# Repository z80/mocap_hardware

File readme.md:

# TODO list for the verion 2.0

-[ ] Separate step down converters for a) MCU and I2C circuits and b) for bluetooth.
-[ ] I2C power filtering capacitors on every outgoung power line on RJ45 sockets.
-[ ] Correct MCU boot mode pins configuration so that it can be updated via USB.
-[ ] Larger filtering capacitors for the bluetooth module.
-[ ] 4 I2C sensors per one RJ45 socket.

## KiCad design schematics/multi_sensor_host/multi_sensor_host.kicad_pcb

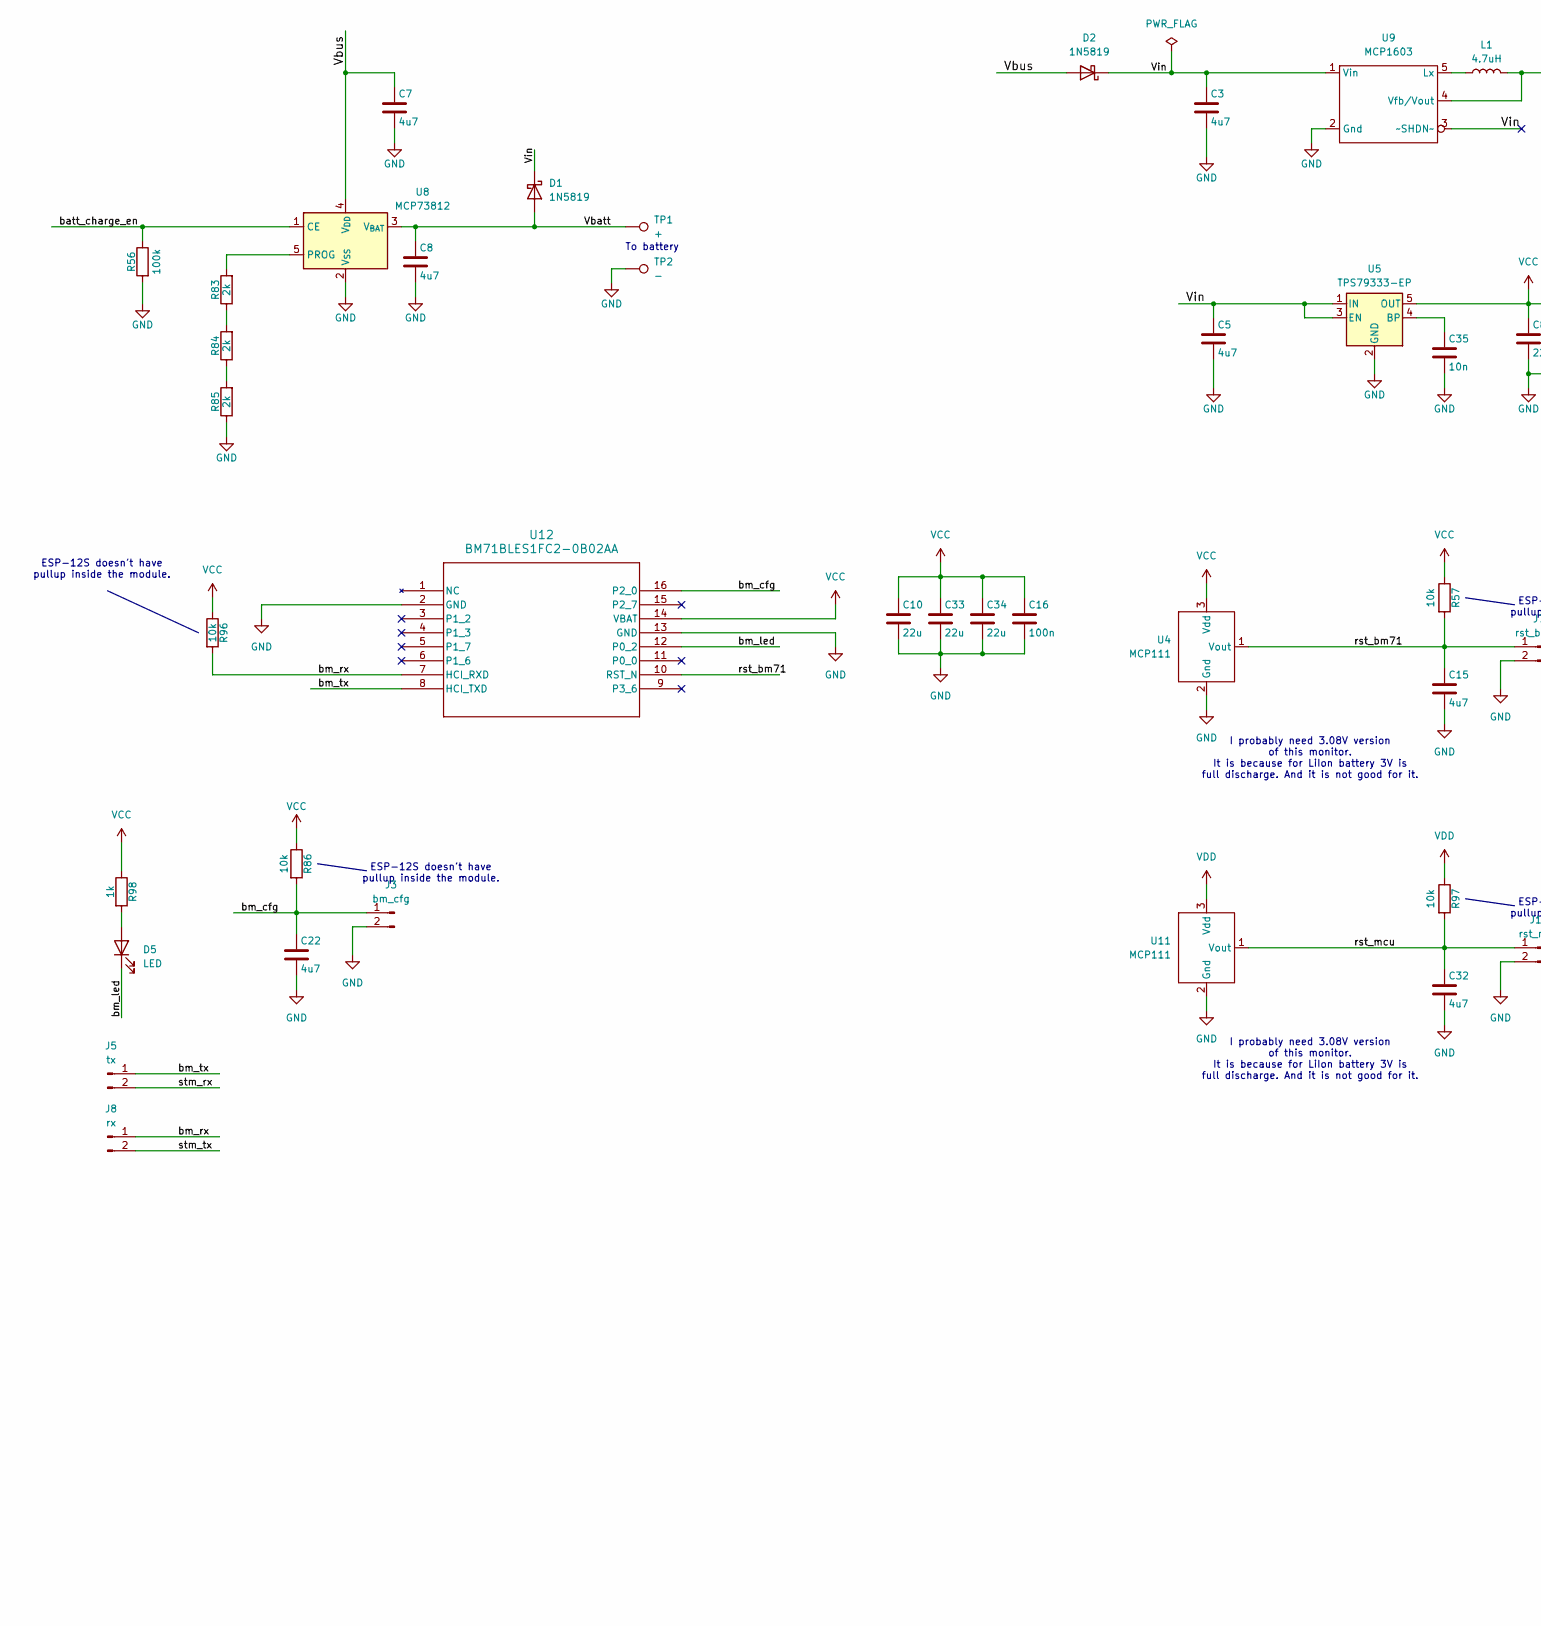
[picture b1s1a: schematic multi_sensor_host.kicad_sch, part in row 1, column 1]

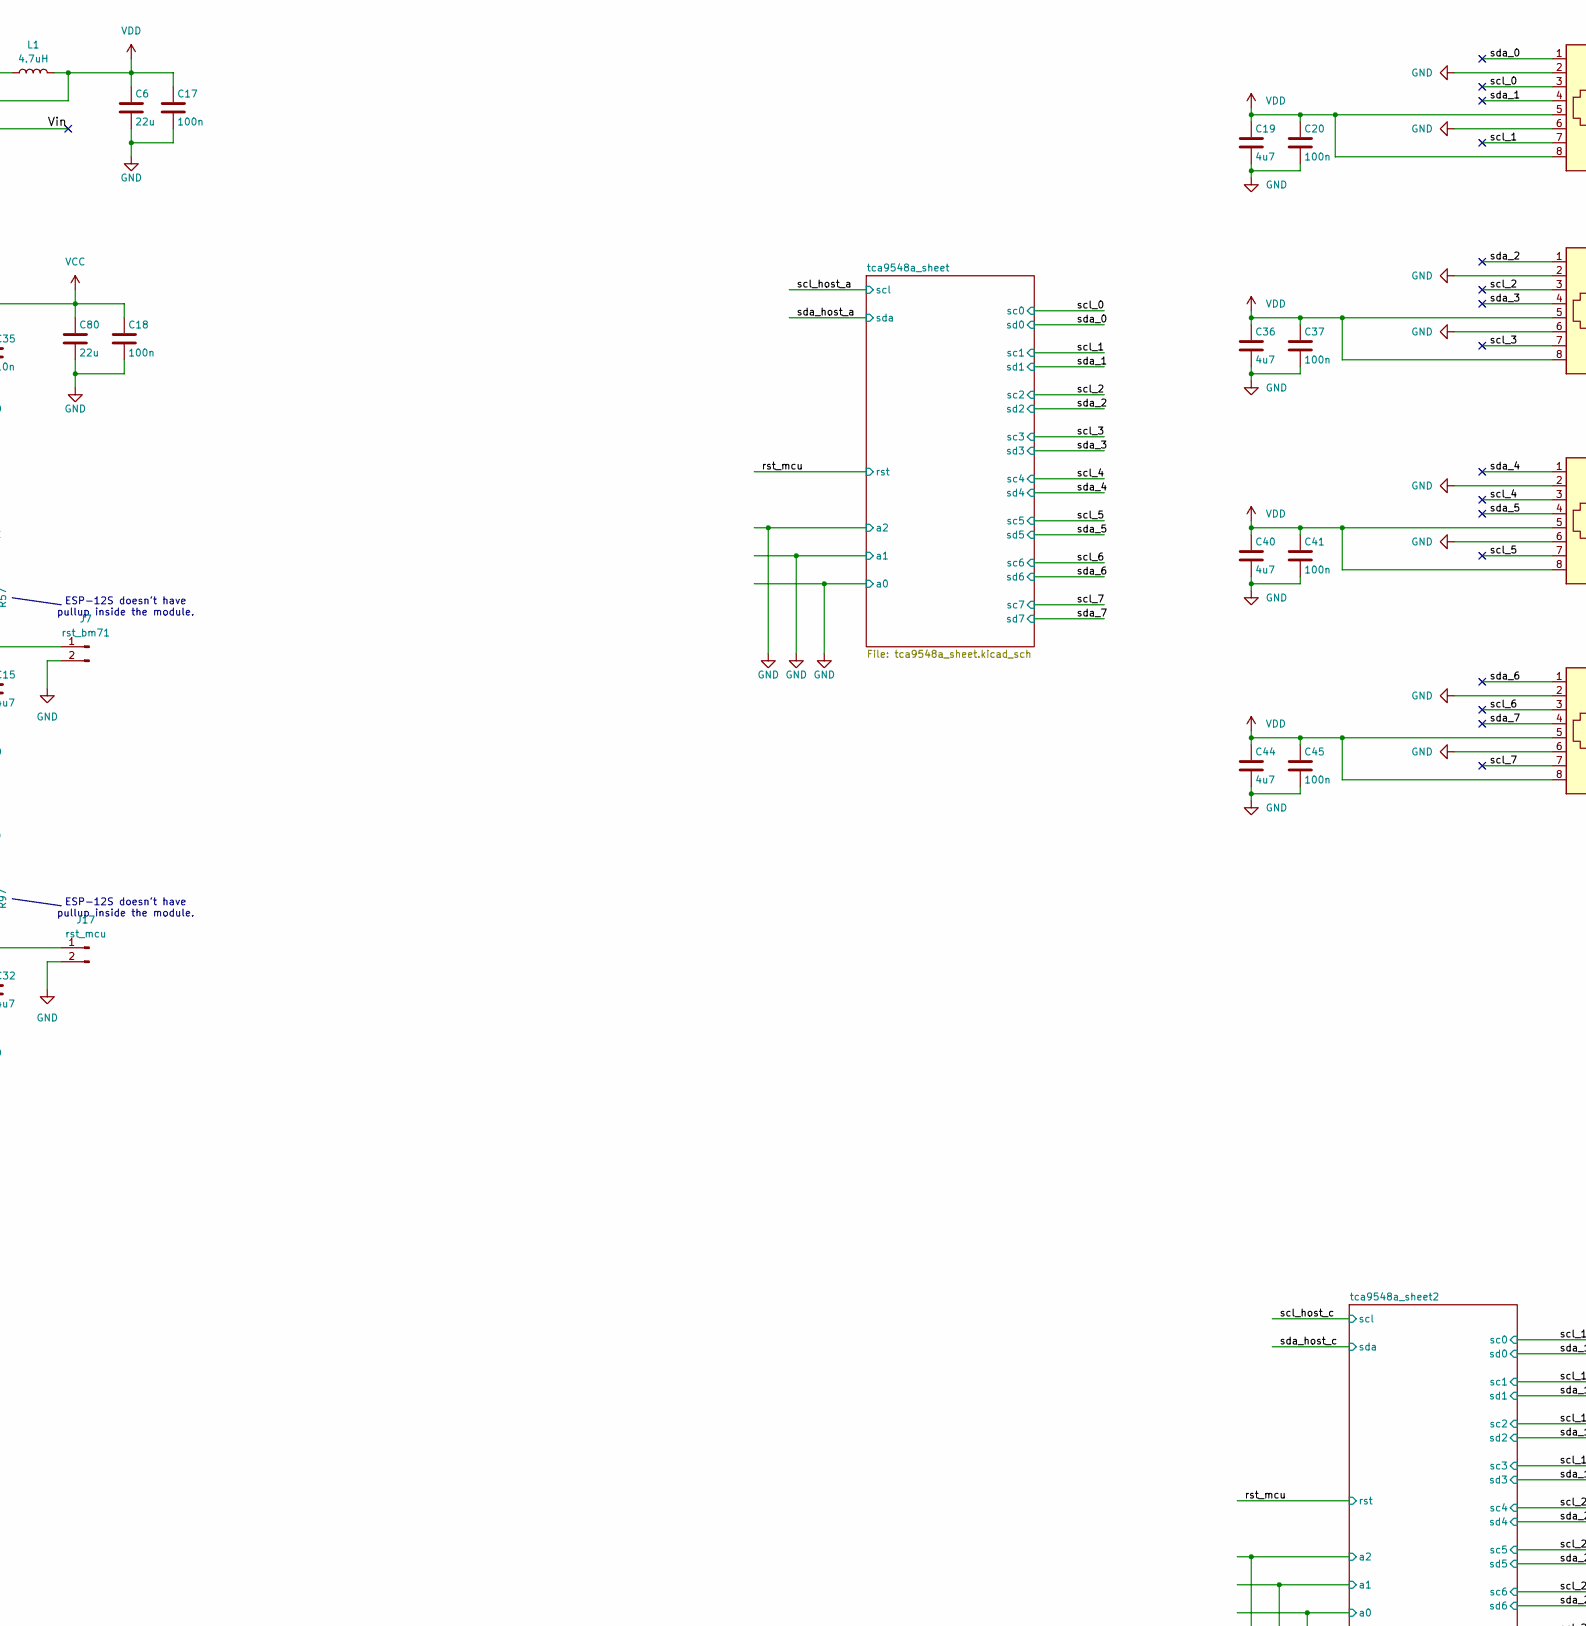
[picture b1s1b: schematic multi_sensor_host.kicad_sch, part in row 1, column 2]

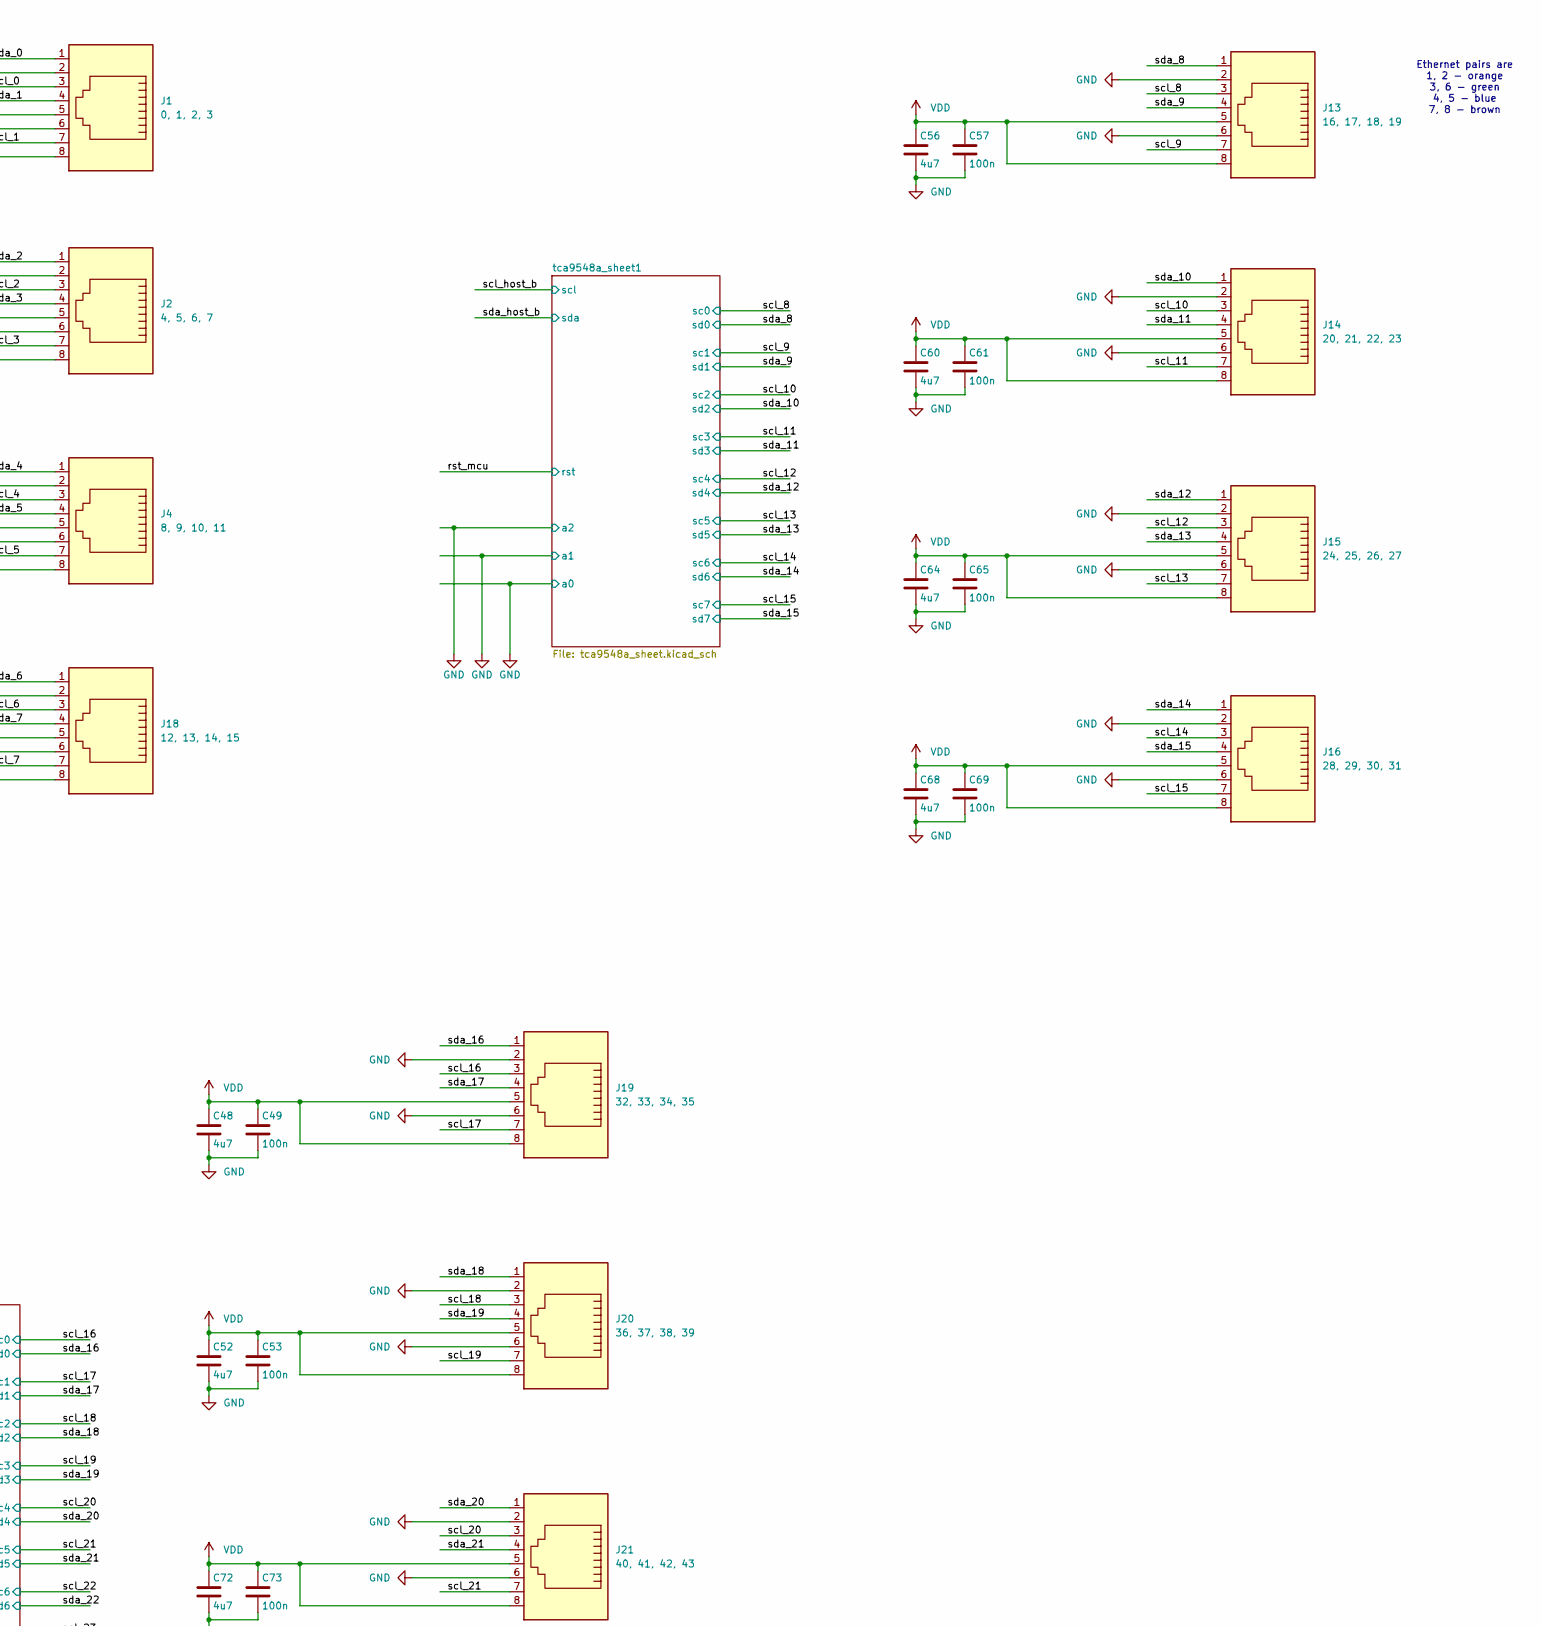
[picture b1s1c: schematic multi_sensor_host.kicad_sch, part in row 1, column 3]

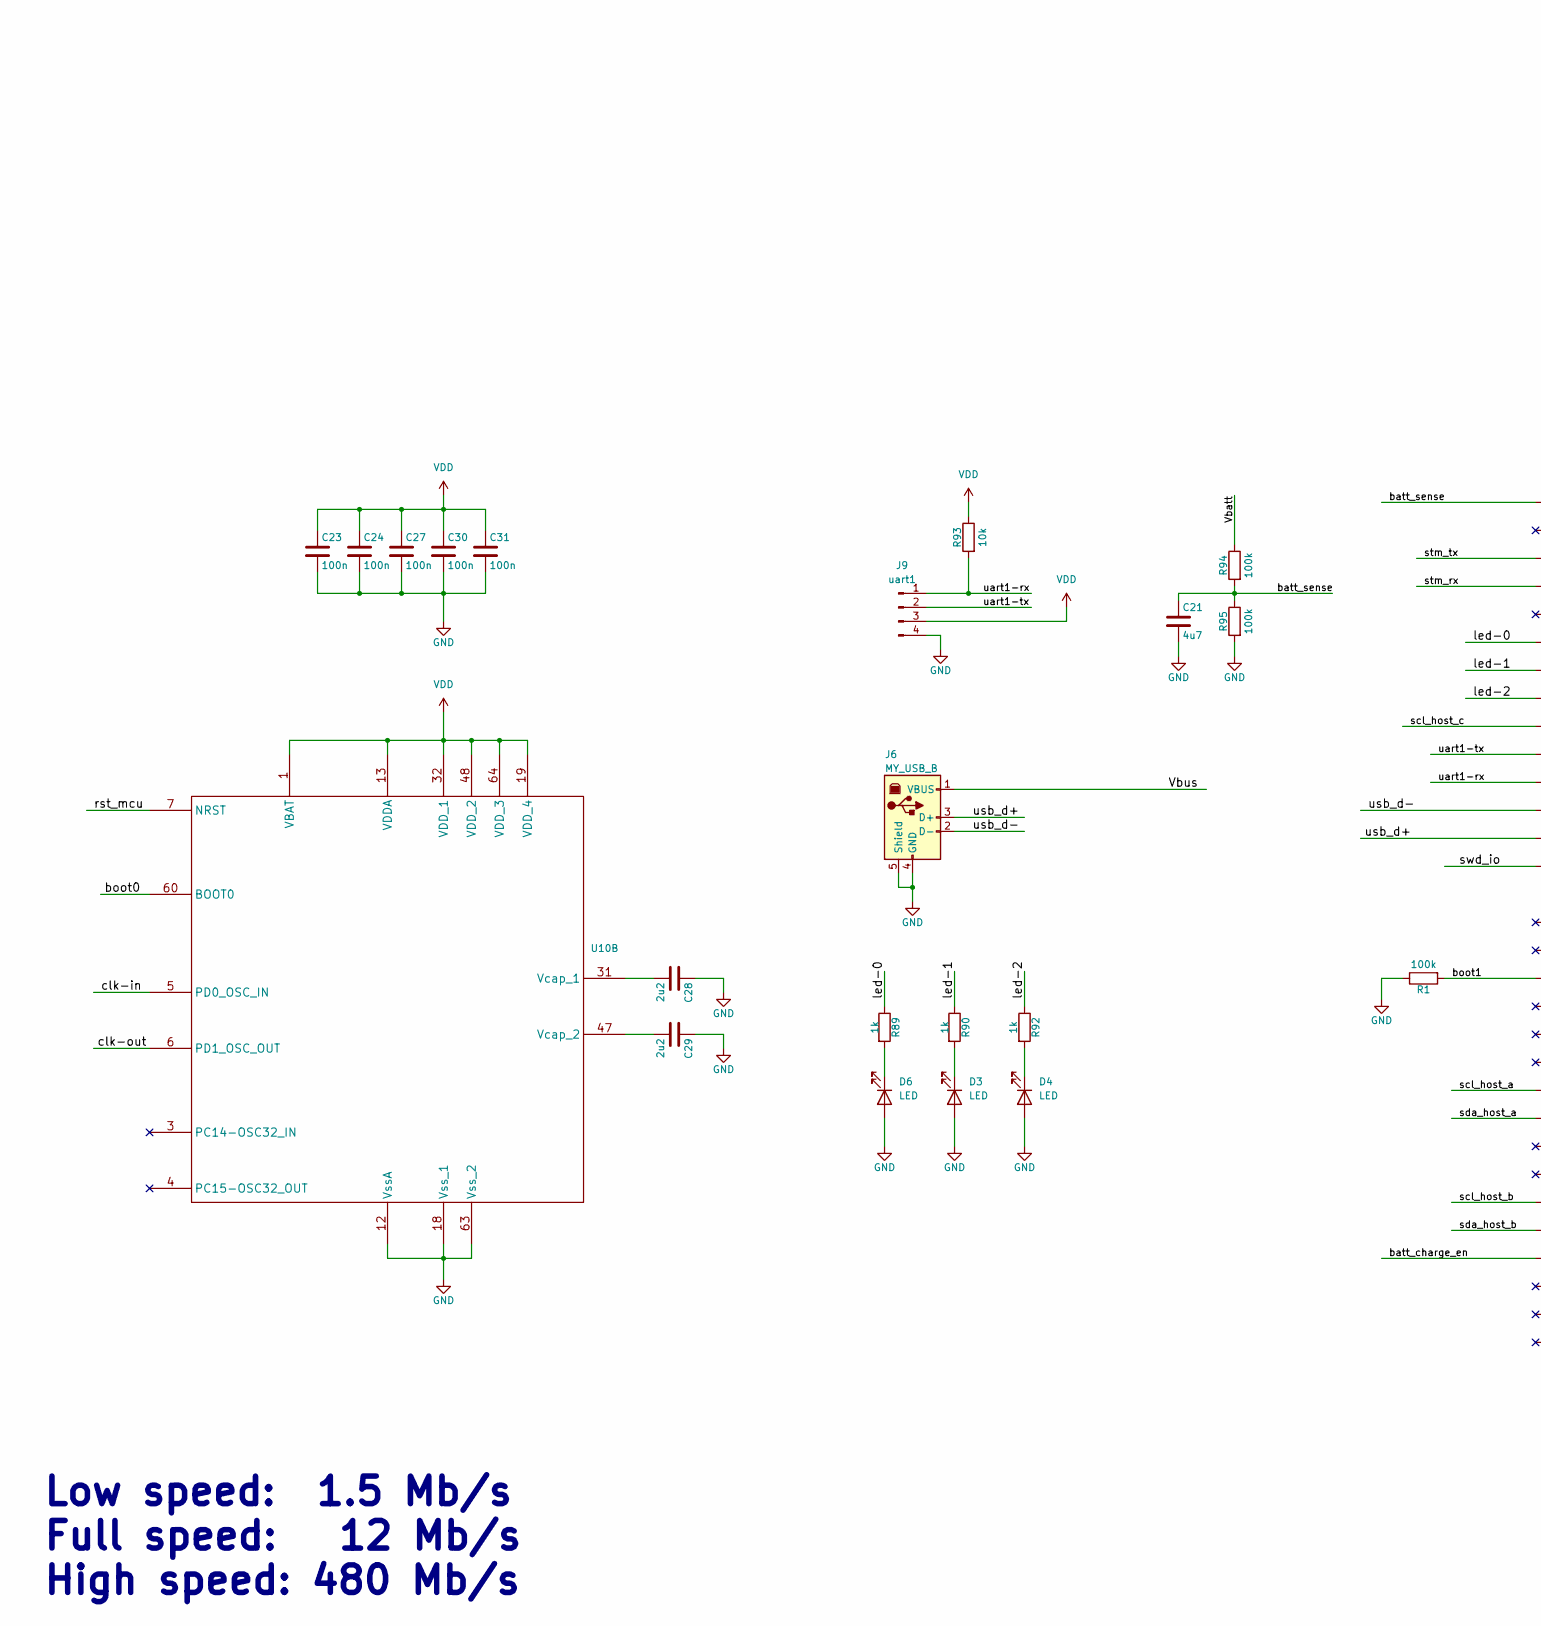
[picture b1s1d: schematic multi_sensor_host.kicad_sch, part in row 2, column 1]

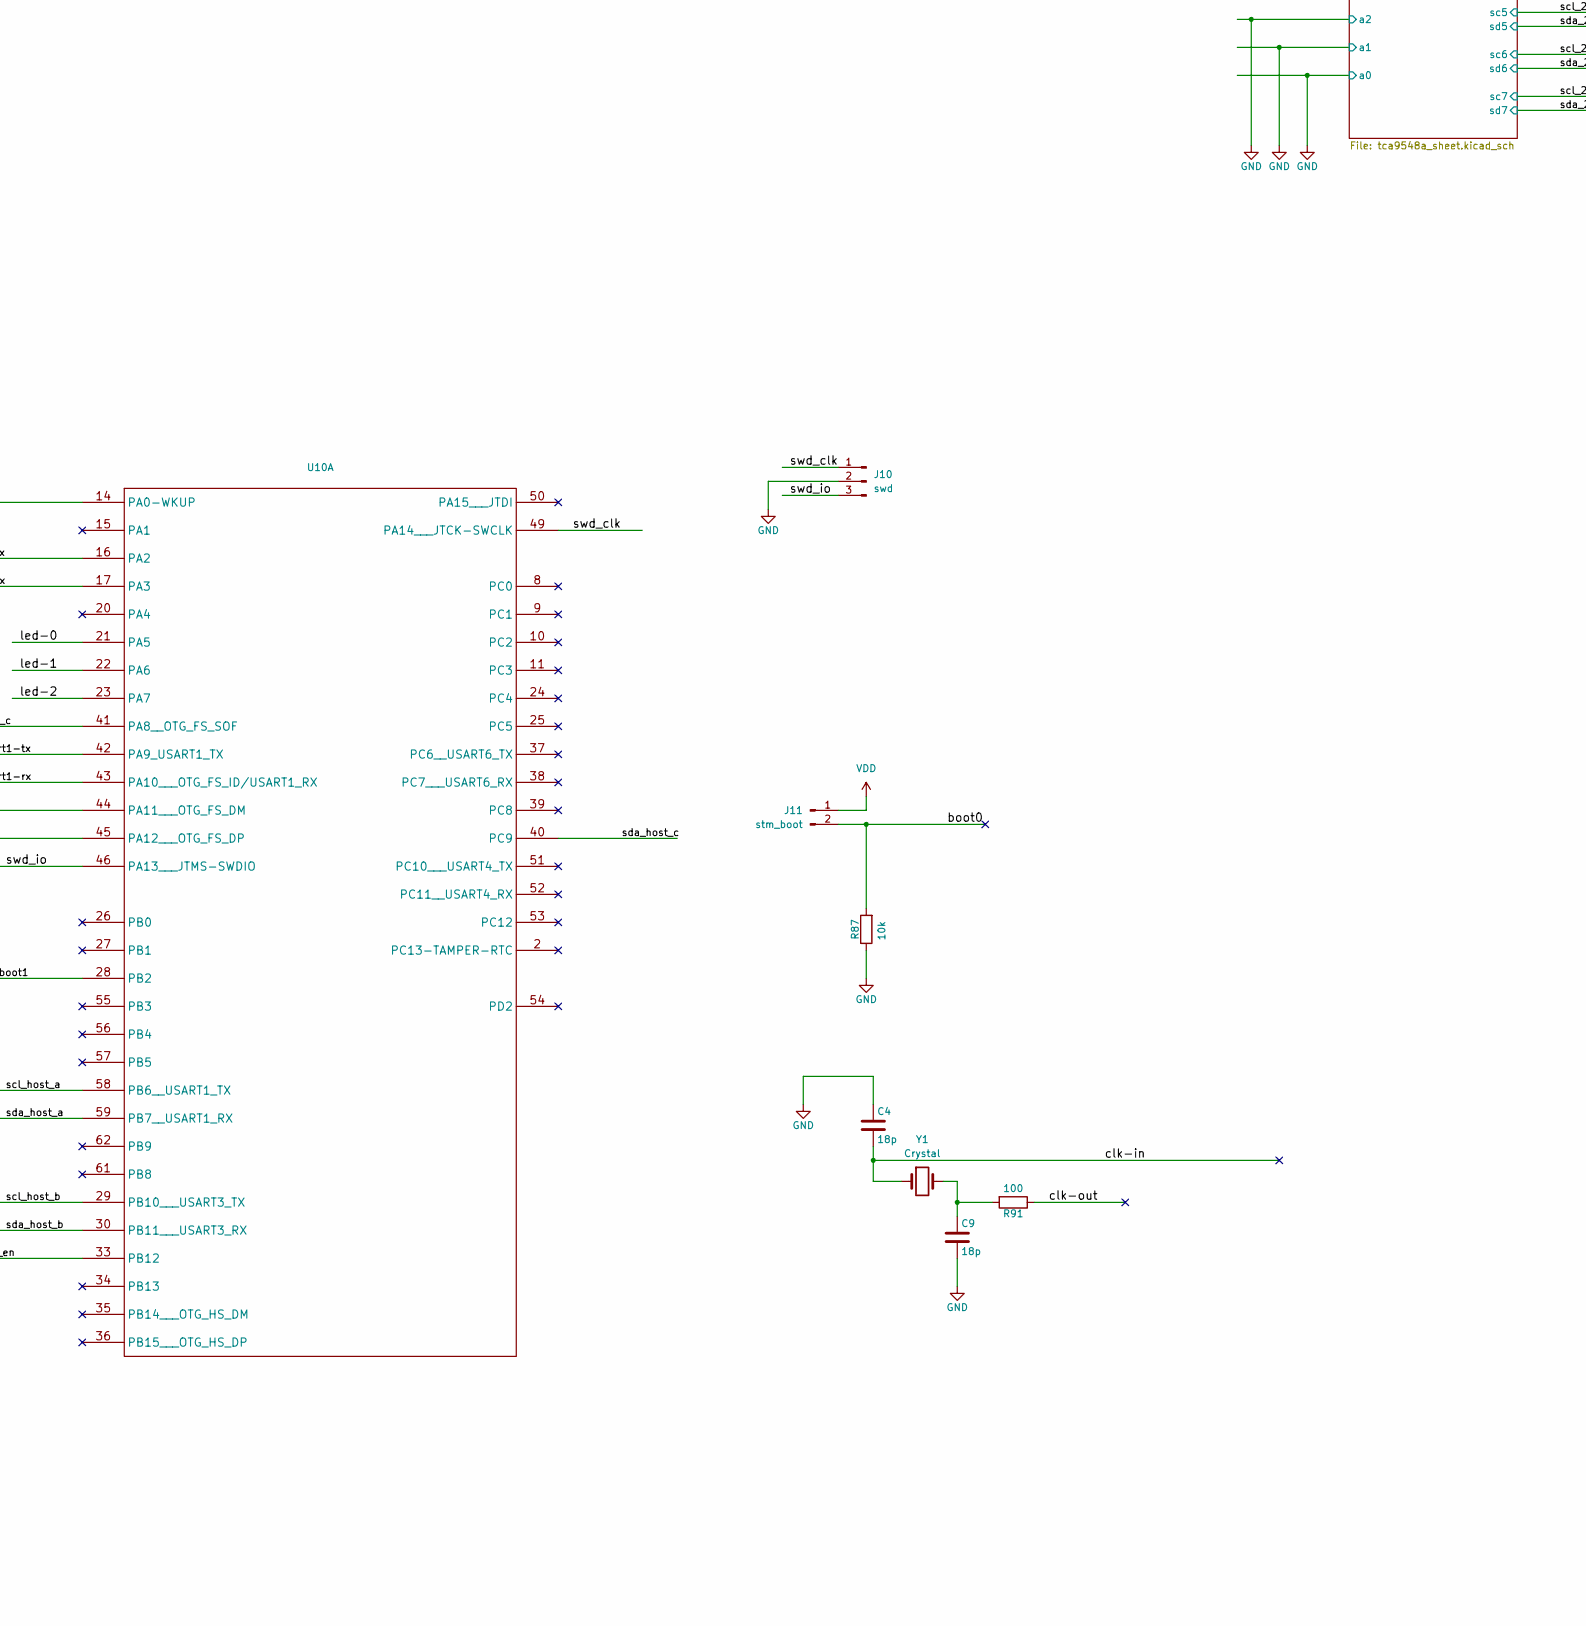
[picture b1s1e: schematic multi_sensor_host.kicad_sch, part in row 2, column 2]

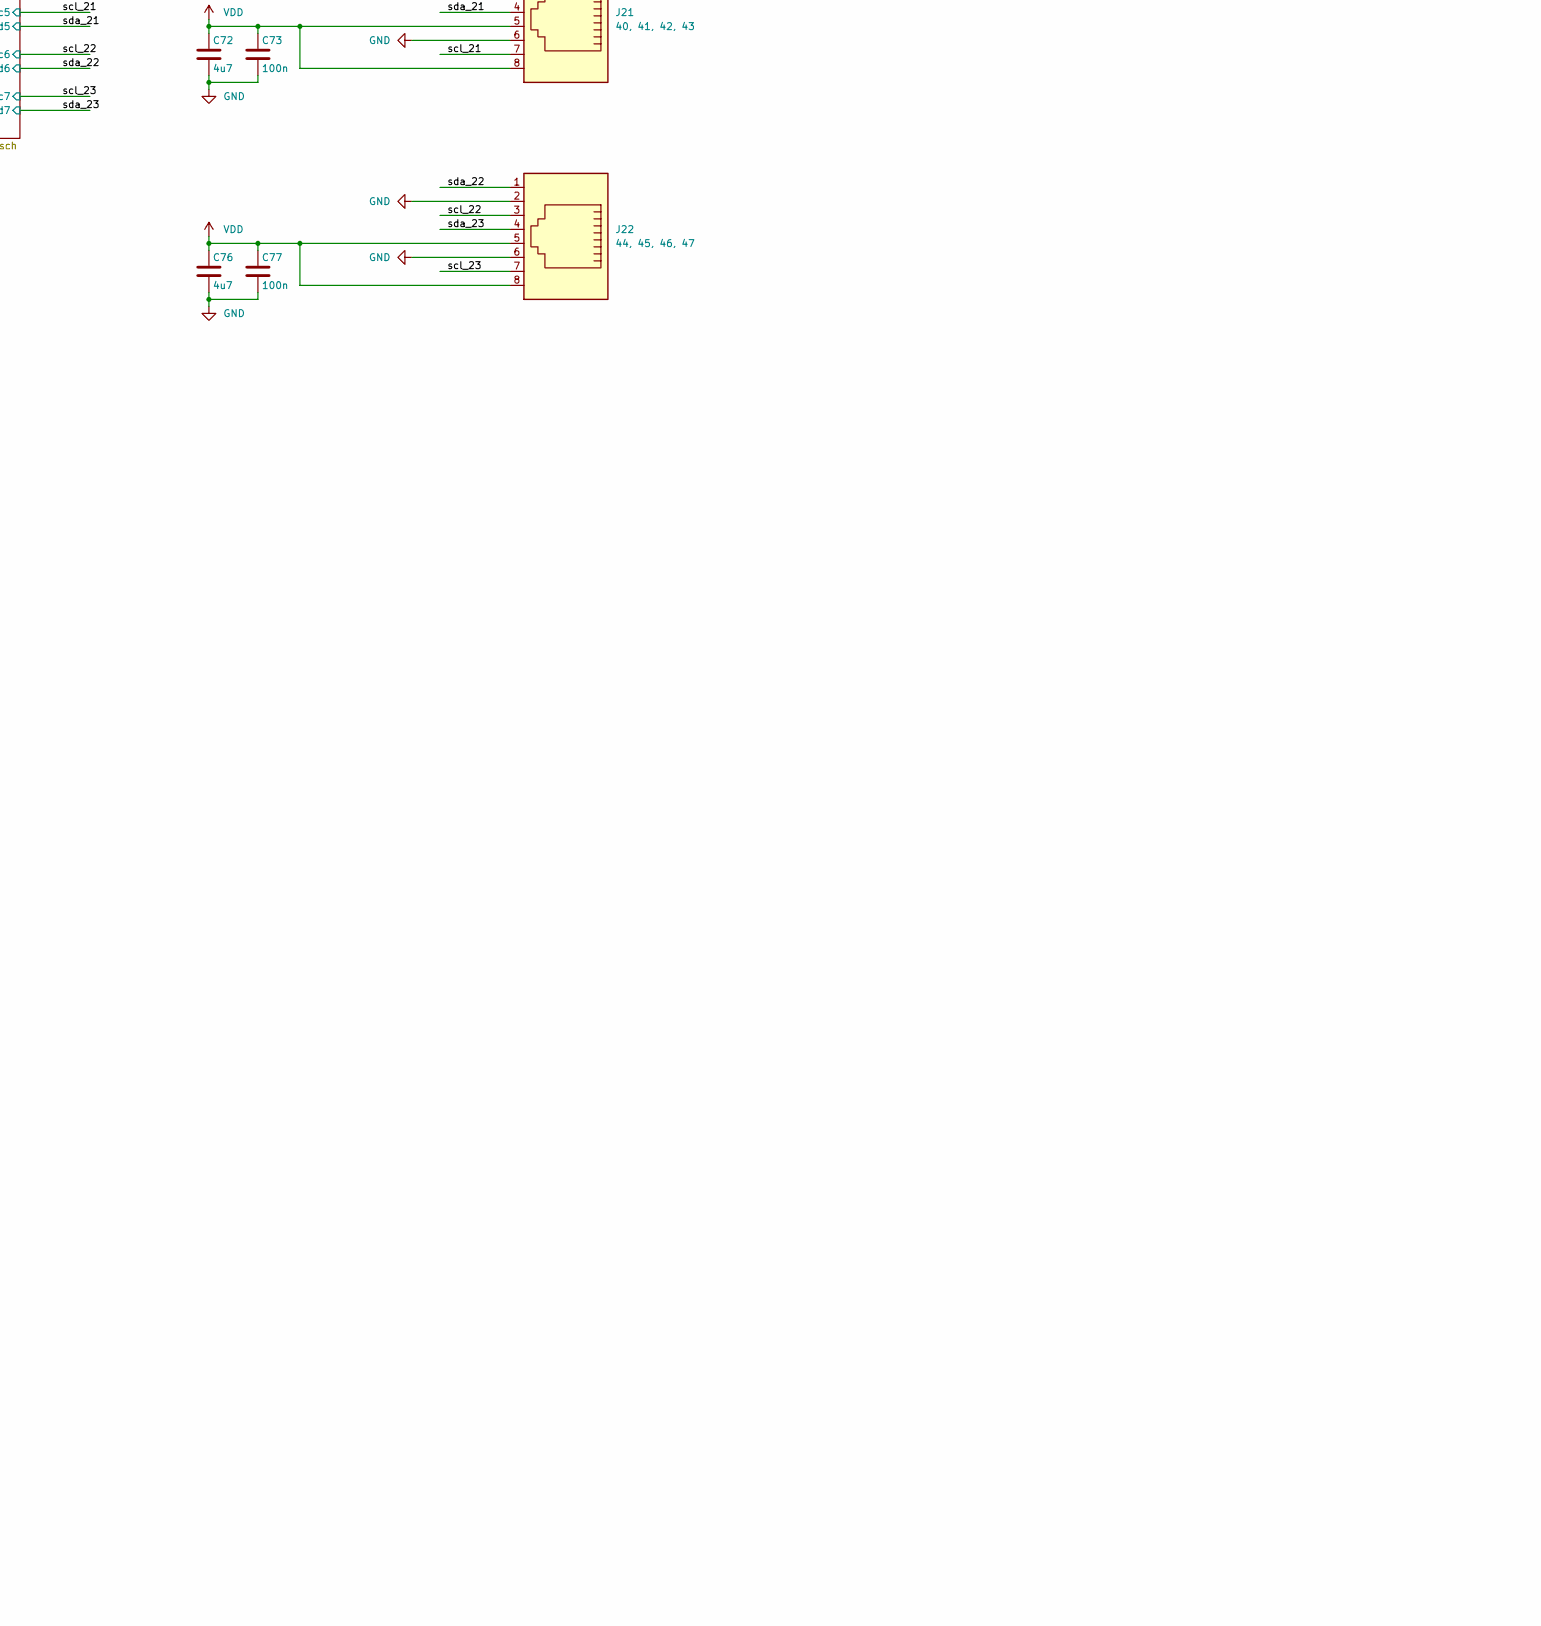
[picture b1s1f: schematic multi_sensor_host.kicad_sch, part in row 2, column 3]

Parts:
C3, C5, C7, C8, C15, C19, C21, C22, C32, C36, C40, C44, C48, C52, C56, C60, C64, C68, C72, C76: 4u7; C_0603_1608Metric
C4, C9: 18p; C_0603_1608Metric
C6, C10, C33, C34, C80: 22u; C_0603_1608Metric
C16, C17, C18, C20, C23, C24, C27, C30, C31, C37, C41, C45, C49, C53, C57, C61, C65, C69, C73, C77: 100n; C_0603_1608Metric
C28, C29: 2u2; C_0603_1608Metric
C35: 10n; C_0603_1608Metric
D1, D2: 1N5819; D_DO-41_SOD81_P7.62mm_Horizontal
D3, D4, D5, D6: LED; LED_D3.0mm
J1: 0, 1, 2, 3; RJ45_OST_PJ012-8P8CX_Vertical
J2: 4, 5, 6, 7; RJ45_OST_PJ012-8P8CX_Vertical
J3: bm_cfg; PinHeader_1x02_P2.54mm_Vertical
J4: 8, 9, 10, 11; RJ45_OST_PJ012-8P8CX_Vertical
J5: tx; PinHeader_1x02_P2.54mm_Vertical
J6: MY_USB_B; USB_B_Lumberg_2411_02_Horizontal
J7: rst_bm71; PinHeader_1x02_P2.54mm_Vertical
J8: rx; PinHeader_1x02_P2.54mm_Vertical
J9: uart1; PinHeader_1x04_P2.54mm_Vertical
J10: swd; PinHeader_1x03_P2.54mm_Vertical
J11: stm_boot; PinHeader_1x02_P2.54mm_Vertical
J13: 16, 17, 18, 19; RJ45_OST_PJ012-8P8CX_Vertical
J14: 20, 21, 22, 23; RJ45_OST_PJ012-8P8CX_Vertical
J15: 24, 25, 26, 27; RJ45_OST_PJ012-8P8CX_Vertical
J16: 28, 29, 30, 31; RJ45_OST_PJ012-8P8CX_Vertical
J17: rst_mcu; PinHeader_1x02_P2.54mm_Vertical
J18: 12, 13, 14, 15; RJ45_OST_PJ012-8P8CX_Vertical
J19: 32, 33, 34, 35; RJ45_OST_PJ012-8P8CX_Vertical
J20: 36, 37, 38, 39; RJ45_OST_PJ012-8P8CX_Vertical
J21: 40, 41, 42, 43; RJ45_OST_PJ012-8P8CX_Vertical
J22: 44, 45, 46, 47; RJ45_OST_PJ012-8P8CX_Vertical
L1: 4.7uH; L_1008_2520Metric
R1, R56, R94, R95: 100k; R_0603_1608Metric
R57, R86, R96, R97: 10k; C_0603_1608Metric
R83, R84, R85: 2k; C_0603_1608Metric
R87, R93: 10k; R_0603_1608Metric
R89, R90, R92: 1k; R_0603_1608Metric
R91: 100; R_0603_1608Metric
R98: 1k; C_0603_1608Metric
TP1: +; Pin_D1.4mm_L8.5mm_W2.8mm_FlatFork
TP2: -; Pin_D1.4mm_L8.5mm_W2.8mm_FlatFork
U4, U11: MCP111; TSOT-23_HandSoldering
U5: TPS79333-EP; SOT-23-5
U8: MCP73812; SOT-23-5
U9: MCP1603; SOT-23-5_HandSoldering
U10: LQFP-64_10x10mm_P0.5mm
U12: BM71BLES1FC2-0B02AA; BM71BLES1FC2_MCH
Y1: Crystal; Crystal_HC52-8mm_Vertical

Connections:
/Vbatt: C8.1, D1.2 (A), R94.1, TP1.1, U8.3 (V_{BAT})
/Vbus: C7.1, D2.2 (A), J6.1 (VBUS), U8.4 (V_{DD})
/Vin: C3.1, C5.1, D1.1 (K), D2.1 (K), U5.1 (IN), U5.3 (EN), U9.1 (Vin), U9.3 (~SHDN~)
/batt_charge_en: R56.1, U8.1 (CE), U10.33 (PB12)
/batt_sense: C21.1, R94.2, R95.1, U10.14 (PA0-WKUP)
/bm_cfg: C22.1, J3.1, R86.2, U12.16 (P2_0)
/bm_led: D5.1 (K), U12.12 (P0_2)
/bm_rx: J8.1, R96.2, U12.7 (HCI_RXD)
/bm_tx: J5.1, U12.8 (HCI_TXD)
/boot0: J11.2, R87.2, U10.60 (BOOT0)
/boot1: R1.2, U10.28 (PB2)
/clk-in: C4.2, U10.5 (PD0_OSC_IN), Y1.1
/clk-out: R91.1, U10.6 (PD1_OSC_OUT)
/led-0: R89.1, U10.21 (PA5)
/led-1: R90.1, U10.22 (PA6)
/led-2: R92.1, U10.23 (PA7)
/rst_bm71: C15.1, J7.1, R57.2, U4.1 (Vout), U12.10 (RST_N)
/rst_mcu: C32.1, J17.1, R97.2, U10.7 (NRST), U11.1 (Vout); also elsewhere on the board
/scl_0: J1.3; also elsewhere on the board
/scl_1: J1.7; also elsewhere on the board
/scl_2: J2.3; also elsewhere on the board
/scl_3: J2.7; also elsewhere on the board
/scl_4: J4.3; also elsewhere on the board
/scl_5: J4.7; also elsewhere on the board
/scl_6: J18.3; also elsewhere on the board
/scl_7: J18.7; also elsewhere on the board
/scl_8: J13.3; also elsewhere on the board
/scl_9: J13.7; also elsewhere on the board
/scl_10: J14.3; also elsewhere on the board
/scl_11: J14.7; also elsewhere on the board
/scl_12: J15.3; also elsewhere on the board
/scl_13: J15.7; also elsewhere on the board
/scl_14: J16.3; also elsewhere on the board
/scl_15: J16.7; also elsewhere on the board
/scl_16: J19.3; also elsewhere on the board
/scl_17: J19.7; also elsewhere on the board
/scl_18: J20.3; also elsewhere on the board
/scl_19: J20.7; also elsewhere on the board
/scl_20: J21.3; also elsewhere on the board
/scl_21: J21.7; also elsewhere on the board
/scl_22: J22.3; also elsewhere on the board
/scl_23: J22.7; also elsewhere on the board
/scl_host_a: U10.58 (PB6__USART1_TX); also elsewhere on the board
/scl_host_b: U10.29 (PB10___USART3_TX); also elsewhere on the board
/scl_host_c: U10.41 (PA8__OTG_FS_SOF); also elsewhere on the board
/sda_0: J1.1; also elsewhere on the board
/sda_1: J1.4; also elsewhere on the board
/sda_2: J2.1; also elsewhere on the board
/sda_3: J2.4; also elsewhere on the board
/sda_4: J4.1; also elsewhere on the board
/sda_5: J4.4; also elsewhere on the board
/sda_6: J18.1; also elsewhere on the board
/sda_7: J18.4; also elsewhere on the board
/sda_8: J13.1; also elsewhere on the board
/sda_9: J13.4; also elsewhere on the board
/sda_10: J14.1; also elsewhere on the board
/sda_11: J14.4; also elsewhere on the board
/sda_12: J15.1; also elsewhere on the board
/sda_13: J15.4; also elsewhere on the board
/sda_14: J16.1; also elsewhere on the board
/sda_15: J16.4; also elsewhere on the board
/sda_16: J19.1; also elsewhere on the board
/sda_17: J19.4; also elsewhere on the board
/sda_18: J20.1; also elsewhere on the board
/sda_19: J20.4; also elsewhere on the board
/sda_20: J21.1; also elsewhere on the board
/sda_21: J21.4; also elsewhere on the board
/sda_22: J22.1; also elsewhere on the board
/sda_23: J22.4; also elsewhere on the board
/sda_host_a: U10.59 (PB7__USART1_RX); also elsewhere on the board
/sda_host_b: U10.30 (PB11___USART3_RX); also elsewhere on the board
/sda_host_c: U10.40 (PC9); also elsewhere on the board
/stm_rx: J5.2, U10.17 (PA3)
/stm_tx: J8.2, U10.16 (PA2)
/swd_clk: J10.1, U10.49 (PA14___JTCK-SWCLK)
/swd_io: J10.3, U10.46 (PA13___JTMS-SWDIO)
/uart1-rx: J9.1, R93.2, U10.43 (PA10___OTG_FS_ID/USART1_RX)
/uart1-tx: J9.2, U10.42 (PA9_USART1_TX)
/usb_d+: J6.3 (D+), U10.45 (PA12___OTG_FS_DP)
/usb_d-: J6.2 (D-), U10.44 (PA11___OTG_FS_DM)
GND: C3.2, C4.1, C5.2, C6.2, C7.2, C8.2, C9.2, C10.2, C15.2, C16.2, C17.2, C18.2, C19.2, C20.2, C21.2, C22.2, C23.2, C24.2, C27.2, C28.1, C29.1, C30.2, C31.2, C32.2, C33.2, C34.2, C35.2, C36.2, C37.2, C40.2, C41.2, C44.2, C45.2, C48.2, C49.2, C52.2, C53.2, C56.2, C57.2, C60.2, C61.2, C64.2, C65.2, C68.2, C69.2, C72.2, C73.2, C76.2, C77.2, C80.2, D3.2 (A), D4.2 (A), D6.2 (A), J1.2, J1.6, J2.2, J2.6, J3.2, J4.2, J4.6, J6.4 (GND), J6.5 (Shield), J7.2, J9.4, J10.2, J13.2, J13.6, J14.2, J14.6, J15.2, J15.6, J16.2, J16.6, J17.2, J18.2, J18.6, J19.2, J19.6, J20.2, J20.6, J21.2, J21.6, J22.2, J22.6, R1.1, R56.2, R85.1, R87.1, R95.2, TP2.1, U4.2 (Gnd), U5.2 (GND), U8.2 (V_{SS}), U9.2 (Gnd), U10.12 (VssA), U10.18 (Vss_1), U10.63 (Vss_2), U11.2 (Gnd), U12.2 (GND), U12.13 (GND); also elsewhere on the board
unnamed: C9.1, R91.2, Y1.2
unnamed: D3.1 (K), R90.2
unnamed: D4.1 (K), R92.2
unnamed: D5.2 (A), R98.2
unnamed: D6.1 (K), R89.2
unnamed: R83.1, R84.2
unnamed: R84.1, R85.2
unnamed: C35.1, U5.4 (BP)
unnamed: R83.2, U8.5 (PROG)
unnamed: L1.1, U9.5 (Lx)
unnamed: C28.2, U10.31 (Vcap_1)
unnamed: C29.2, U10.47 (Vcap_2)
VCC: C10.1, C16.1, C18.1, C33.1, C34.1, C80.1, R57.1, R86.1, R96.1, R98.1, U4.3 (Vdd), U5.5 (OUT), U12.14 (VBAT)
VDD: C6.1, C17.1, C19.1, C20.1, C23.1, C24.1, C27.1, C30.1, C31.1, C36.1, C37.1, C40.1, C41.1, C44.1, C45.1, C48.1, C49.1, C52.1, C53.1, C56.1, C57.1, C60.1, C61.1, C64.1, C65.1, C68.1, C69.1, C72.1, C73.1, C76.1, C77.1, J1.5, J1.8, J2.5, J2.8, J4.5, J4.8, J9.3, J11.1, J13.5, J13.8, J14.5, J14.8, J15.5, J15.8, J16.5, J16.8, J18.5, J18.8, J19.5, J19.8, J20.5, J20.8, J21.5, J21.8, J22.5, J22.8, L1.2, R93.1, R97.1, U9.4 (Vfb/Vout), U10.1 (VBAT), U10.13 (VDDA), U10.19 (VDD_4), U10.32 (VDD_1), U10.48 (VDD_2), U10.64 (VDD_3), U11.3 (Vdd); also elsewhere on the board

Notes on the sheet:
ESP-12S doesn't have pullup inside the module.
Ethernet pairs are 1, 2 - orange 3, 6 - green 4, 5 - blue 7, 8 - brown
I probably need 3.08V version of this monitor. It is because for LiIon battery 3V is full discharge. And it is not good for it.
To battery
Low speed: 1.5 Mb/s Full speed: 12 Mb/s High speed: 480 Mb/s
